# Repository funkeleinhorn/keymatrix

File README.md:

# Keymatrix

Keymatrix PCB providing a numpad typical for phones with a call, menu and hang up button.
The keymatrix features diodes to prevent ghosting effects.

This project is licensed as open hardware. See LICENSE.txt for details.

## Images

Here you can see how the PCB looks:

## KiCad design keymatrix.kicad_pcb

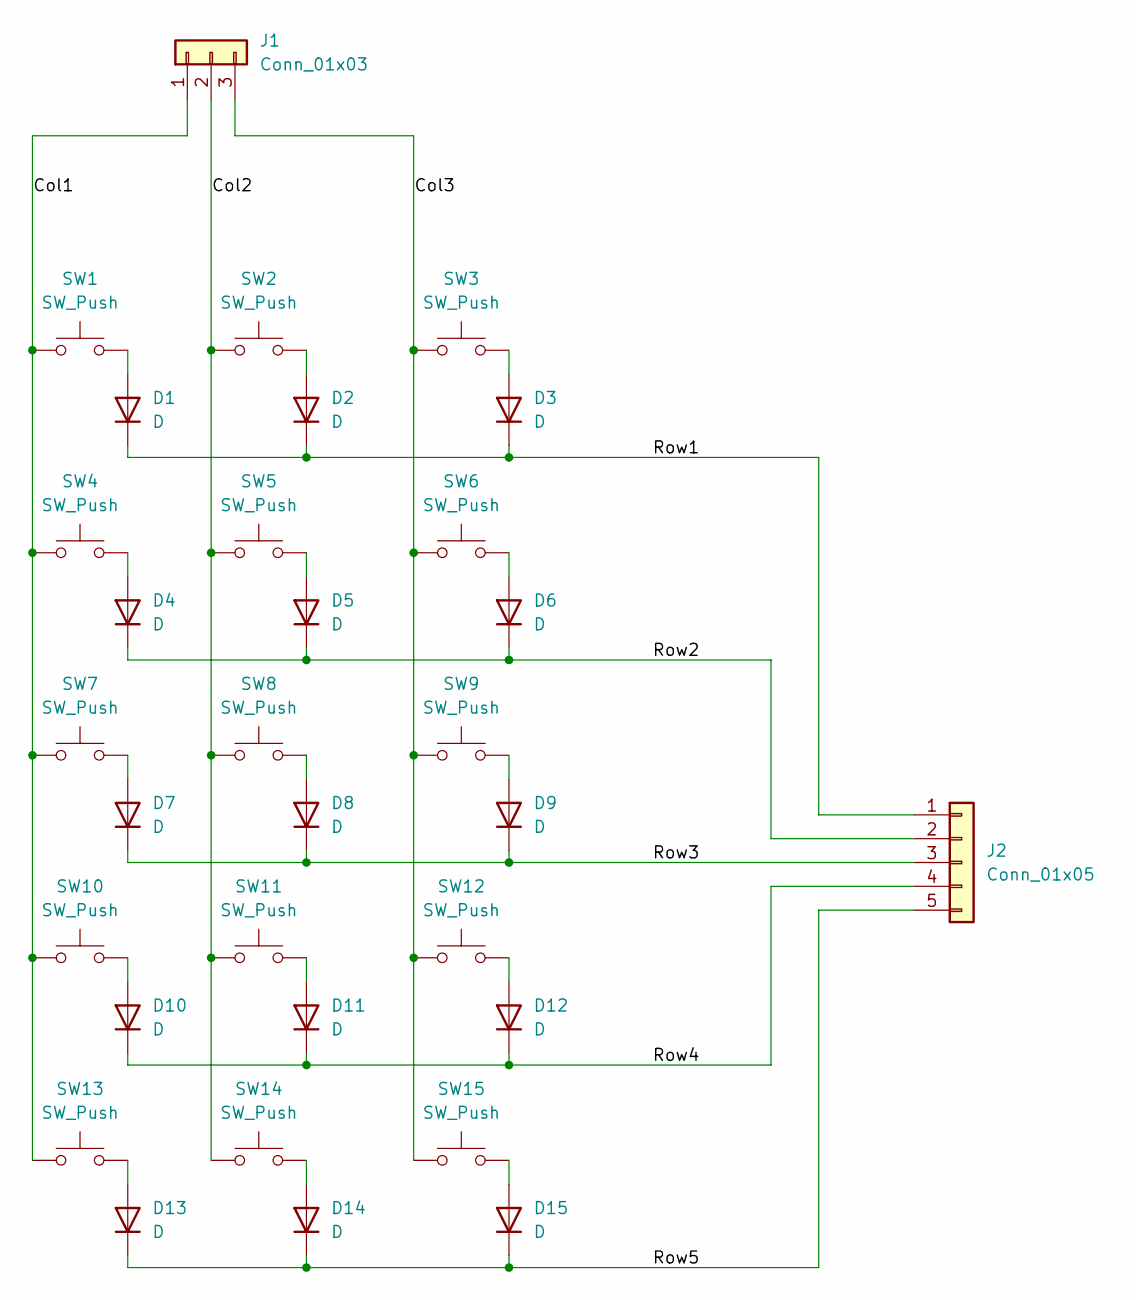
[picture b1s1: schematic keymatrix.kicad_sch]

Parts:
D1, D2, D3, D4, D5, D6, D7, D8, D9, D10, D11, D12, D13, D14, D15: D; D_MiniMELF
J1: Conn_01x03; PinHeader_1x03_P2.54mm_Vertical
J2: Conn_01x05; PinHeader_1x05_P2.54mm_Vertical
SW1, SW2, SW3, SW4, SW5, SW6, SW7, SW8, SW9, SW10, SW11, SW12, SW13, SW14, SW15: SW_Push; SW_SPST_PTS645

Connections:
/Col1: J1.1, SW1.1, SW4.1, SW7.1, SW10.1, SW13.1
/Col2: J1.2, SW2.1, SW5.1, SW8.1, SW11.1, SW14.1
/Col3: J1.3, SW3.1, SW6.1, SW9.1, SW12.1, SW15.1
/Row1: D1.1 (K), D2.1 (K), D3.1 (K), J2.1
/Row2: D4.1 (K), D5.1 (K), D6.1 (K), J2.2
/Row3: D7.1 (K), D8.1 (K), D9.1 (K), J2.3
/Row4: D10.1 (K), D11.1 (K), D12.1 (K), J2.4
/Row5: D13.1 (K), D14.1 (K), D15.1 (K), J2.5
unnamed: D1.2 (A), SW1.2
unnamed: D2.2 (A), SW2.2
unnamed: D3.2 (A), SW3.2
unnamed: D4.2 (A), SW4.2
unnamed: D5.2 (A), SW5.2
unnamed: D6.2 (A), SW6.2
unnamed: D7.2 (A), SW7.2
unnamed: D8.2 (A), SW8.2
unnamed: D9.2 (A), SW9.2
unnamed: D10.2 (A), SW10.2
unnamed: D11.2 (A), SW11.2
unnamed: D12.2 (A), SW12.2
unnamed: D13.2 (A), SW13.2
unnamed: D14.2 (A), SW14.2
unnamed: D15.2 (A), SW15.2

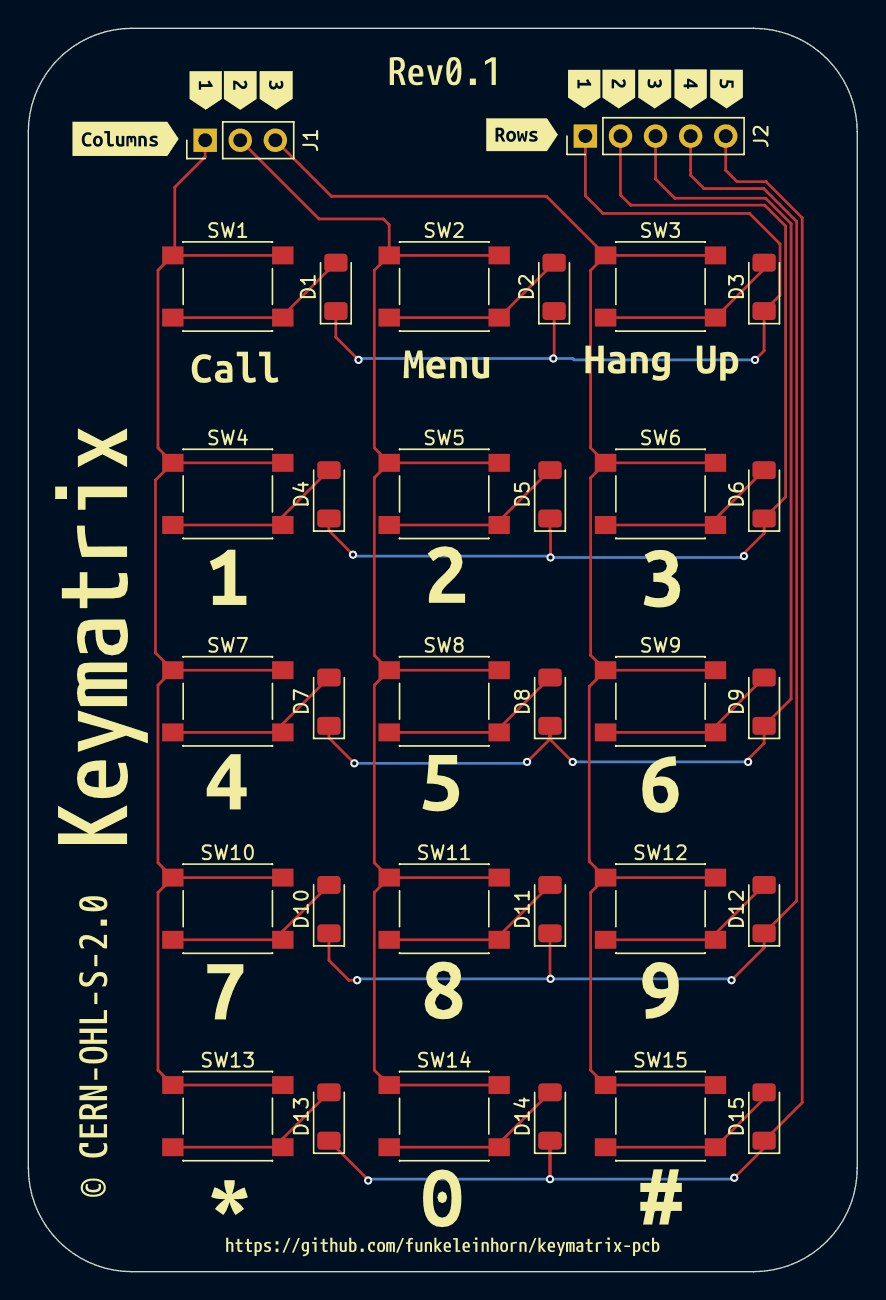
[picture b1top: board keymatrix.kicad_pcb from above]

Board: 2 copper layers, 60.0 x 90.0 mm, 61 parts (0 on the bottom side), 23 nets.

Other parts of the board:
kibuzzard-67EF9C02: G***; kibuzzard-67EF9C02
kibuzzard-67EF9C20: G***; kibuzzard-67EF9C20
kibuzzard-67EF9C24: G***; kibuzzard-67EF9C24
kibuzzard-67EF94E3: G***; kibuzzard-67EF94E3
kibuzzard-67EF94F8: G***; kibuzzard-67EF94F8
kibuzzard-67EF95BB: G***; kibuzzard-67EF95BB
kibuzzard-67EF95DE: G***; kibuzzard-67EF95DE
kibuzzard-67EF95EE: G***; kibuzzard-67EF95EE
kibuzzard-67EF97B6, kibuzzard-67EF97B6#2: G***; kibuzzard-67EF97B6
kibuzzard-67EF97CE, kibuzzard-67EF97CE#2: G***; kibuzzard-67EF97CE
kibuzzard-67EF97D2, kibuzzard-67EF97D2#2: G***; kibuzzard-67EF97D2
kibuzzard-67EF951D: G***; kibuzzard-67EF951D
kibuzzard-67EF953E: G***; kibuzzard-67EF953E
kibuzzard-67EF957E: G***; kibuzzard-67EF957E
kibuzzard-67EF9502: G***; kibuzzard-67EF9502
kibuzzard-67EF9511: G***; kibuzzard-67EF9511
kibuzzard-67EF9529: G***; kibuzzard-67EF9529
kibuzzard-67EF9534: G***; kibuzzard-67EF9534
kibuzzard-67EF9547: G***; kibuzzard-67EF9547
kibuzzard-67EF9551: G***; kibuzzard-67EF9551
kibuzzard-67EF9577: G***; kibuzzard-67EF9577
kibuzzard-67EF9854: G***; kibuzzard-67EF9854
kibuzzard-67F106E2: G***; kibuzzard-67F106E2
kibuzzard-67F1071B: G***; kibuzzard-67F1071B
kibuzzard-67F1073F: G***; kibuzzard-67F1073F
kibuzzard-67F10650: G***; kibuzzard-67F10650

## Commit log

2025-04-18 chore: update schematic PDF [skip ci]
